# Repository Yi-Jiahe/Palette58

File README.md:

# Palette 58

My first (to-be) split ergonomic keyboard.

4x6 column staggered board with 5 key thumb cluster utilizing low profile switches.

The Palette 58 is meant to be an introductory keyboard, heavily inspired by the Sofle.

It includes a number row and additional outer pinky column to support a wider range of layouts to allow for experimentation.

Compared to the Sofle, it features a more aggressive pinky stagger and no additional flex key.

No LEDs because of the added complexity and cost.

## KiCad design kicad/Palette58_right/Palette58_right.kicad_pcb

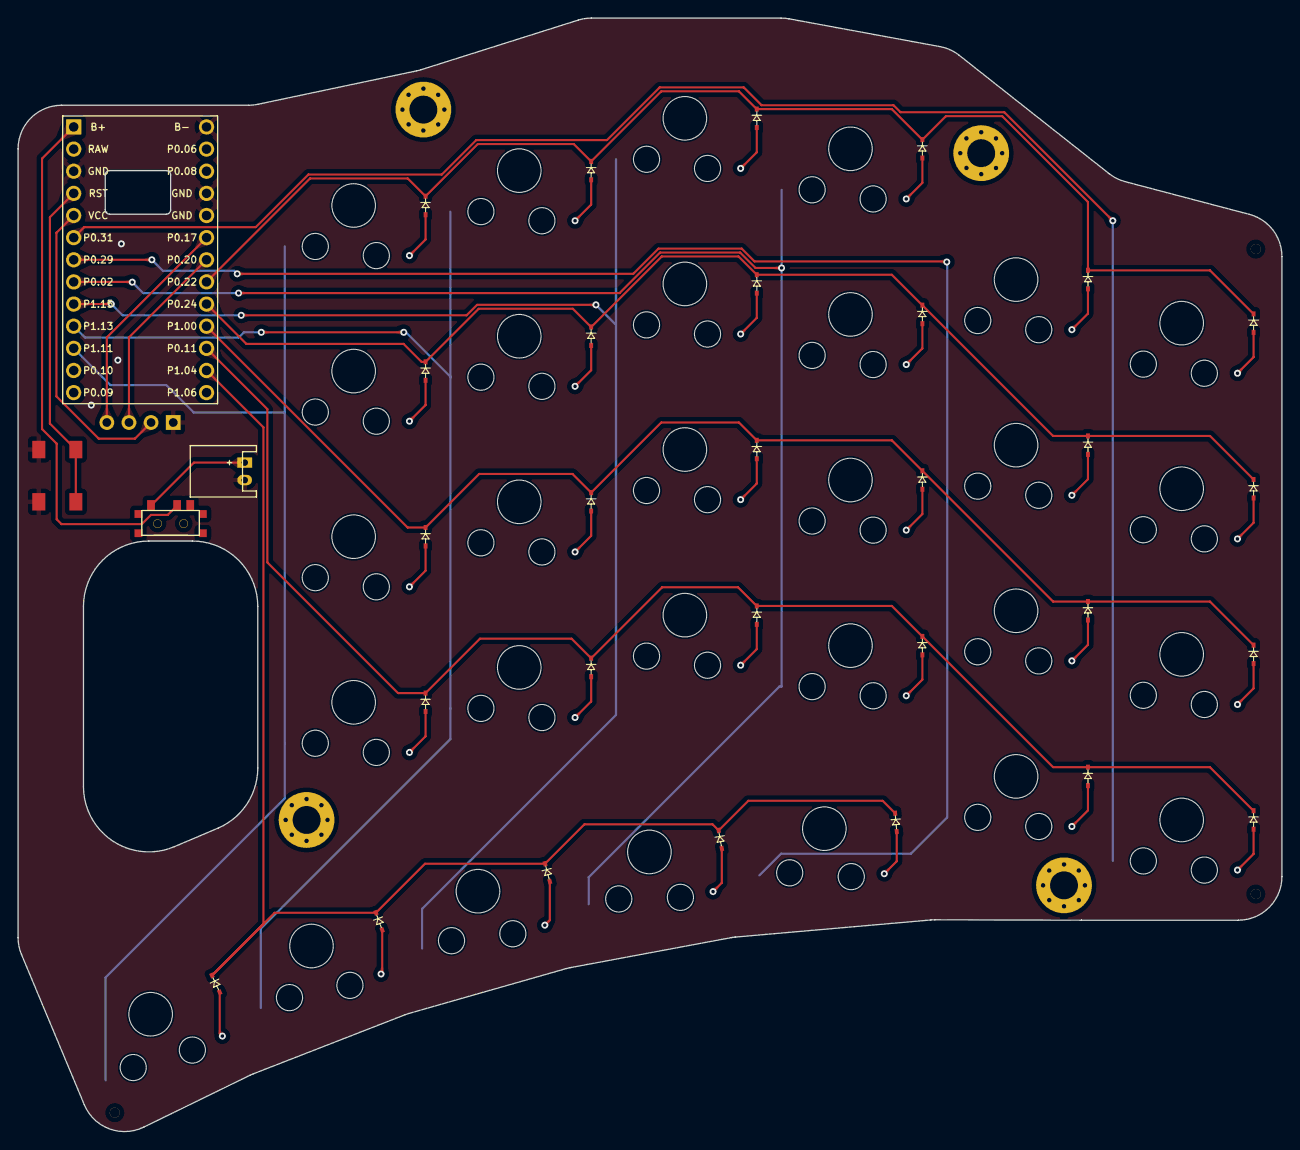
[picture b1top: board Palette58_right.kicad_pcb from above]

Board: 2 copper layers, 145.0 x 127.8 mm, 66 parts (0 on the bottom side), 47 nets.

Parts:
D1, D2, D3, D4, D5, D6, D7, D8, D9, D10, D11, D12, D13, D14, D15, D16, D17, D18, D19, D20, D21, D22, D23, D24, D25, D26, D27, D28, D29: 1N4148; ComboDiode
JST1: JST_PH_S2B-PH-K_02x2.00mm_Angled
MCU1: nice!nanov2
OLED1: OLED; OLED_headers
S1, S2, S3, S4, S5, S6, S7, S8, S9, S10, S11, S12, S13, S14, S15, S16, S17, S18, S19, S20, S21, S22, S23, S24, S25, S26, S27, S28, S29: Gaeteron_low_profile
SW1: MSK12C02-HB; SPDT_C128955
SW2: TS-1187A-B-A-B; PushSwitch
_34, _35, _36: ToolingHole

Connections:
B+: MCU1.1, SW1.2
GND: JST1.2, MCU1.3, MCU1.14, MCU1.17, MCU1.18, OLED1.1, SW2.3, SW2.4
JST+: JST1.1, SW1.1
RST: MCU1.4, SW2.1, SW2.2
SCL: MCU1.20, OLED1.3
SDA: MCU1.19, OLED1.4
VCC: MCU1.5, OLED1.2
col_1: MCU1.6, S1.1, S2.1, S3.1, S4.1
col_2: MCU1.7, S5.1, S6.1, S7.1, S8.1, S25.1
col_3: MCU1.8, S9.1, S10.1, S11.1, S12.1, S26.1
col_4: MCU1.9, S13.1, S14.1, S15.1, S16.1, S27.1
col_5: MCU1.10, S17.1, S18.1, S19.1, S20.1, S28.1
col_6: MCU1.11, S21.1, S22.1, S23.1, S24.1, S29.1
mirror_home_cluster: D28.2, S28.2
mirror_index_bottom: D17.2, S17.2
mirror_index_home: D18.2, S18.2
mirror_index_num: D20.2, S20.2
mirror_index_top: D19.2, S19.2
mirror_inner_bottom: D21.2, S21.2
mirror_inner_cluster: D29.2, S29.2
mirror_inner_home: D22.2, S22.2
mirror_inner_num: D24.2, S24.2
mirror_inner_top: D23.2, S23.2
mirror_middle_bottom: D13.2, S13.2
mirror_middle_home: D14.2, S14.2
mirror_middle_num: D16.2, S16.2
mirror_middle_top: D15.2, S15.2
mirror_outer-2_cluster: D26.2, S26.2
mirror_outer-3_cluster: D25.2, S25.2
mirror_outer_bottom: D1.2, S1.2
mirror_outer_cluster: D27.2, S27.2
mirror_outer_home: D2.2, S2.2
mirror_outer_num: D4.2, S4.2
mirror_outer_top: D3.2, S3.2
mirror_pinky_bottom: D5.2, S5.2
mirror_pinky_home: D6.2, S6.2
mirror_pinky_num: D8.2, S8.2
mirror_pinky_top: D7.2, S7.2
mirror_ring_bottom: D9.2, S9.2
mirror_ring_home: D10.2, S10.2
mirror_ring_num: D12.2, S12.2
mirror_ring_top: D11.2, S11.2
row_1: D4.1, D8.1, D12.1, D16.1, D20.1, D24.1, MCU1.21
row_2: D3.1, D7.1, D11.1, D15.1, D19.1, D23.1, MCU1.22
row_3: D2.1, D6.1, D10.1, D14.1, D18.1, D22.1, MCU1.23
row_4: D1.1, D5.1, D9.1, D13.1, D17.1, D21.1, MCU1.24
row_5: D25.1, D26.1, D27.1, D28.1, D29.1, MCU1.25

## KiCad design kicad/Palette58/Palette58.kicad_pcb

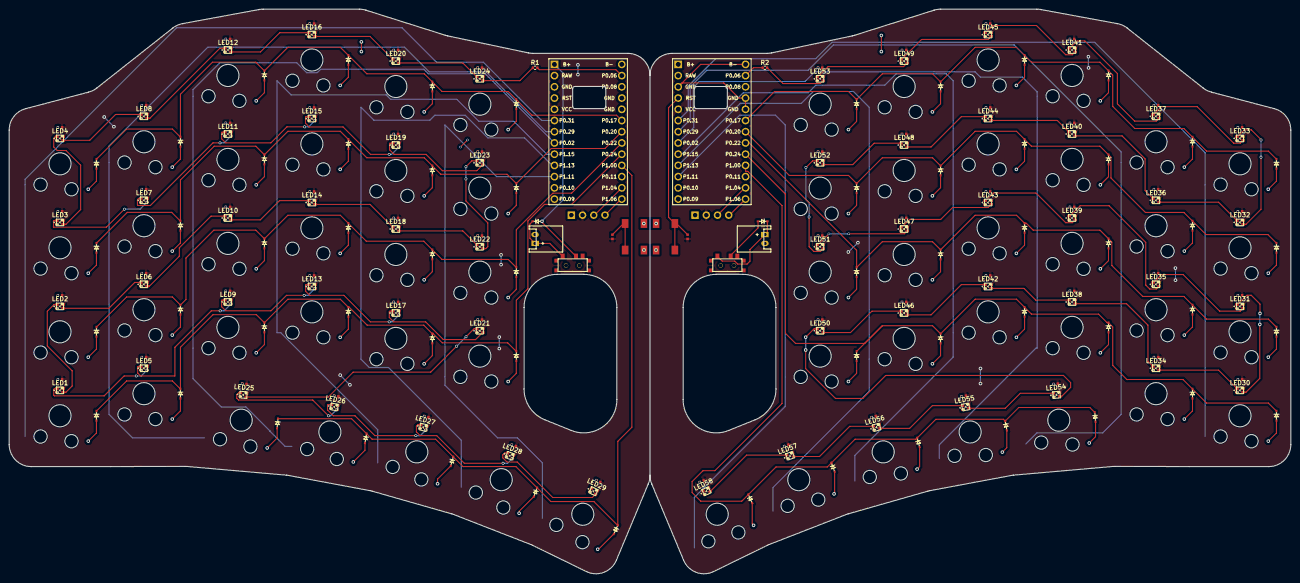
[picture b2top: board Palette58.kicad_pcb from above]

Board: 2 copper layers, 290.0 x 127.8 mm, 248 parts (0 on the bottom side), 140 nets.

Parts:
C1, C2, C3, C4, C5, C6, C7, C8, C9, C10, C11, C12, C13, C14, C15, C16, C17, C18, C19, C20, C21, C22, C23, C24, C25, C26, C27, C28, C29, C30, C31, C32, C33, C34, C35, C36, C37, C38, C39, C40, C41, C42, C43, C44, C45, C46, C47, C48, C49, C50, C51, C52, C53, C54, C55, C56, C57, C58: 100nF; Capacitor
D1, D2, D3, D4, D5, D6, D7, D8, D9, D10, D11, D12, D13, D14, D15, D16, D17, D18, D19, D20, D21, D22, D23, D24, D25, D26, D27, D28, D29, D30, D31, D32, D33, D34, D35, D36, D37, D38, D39, D40, D41, D42, D43, D44, D45, D46, D47, D48, D49, D50, D51, D52, D53, D54, D55, D56, D57, D58: 1N4148; ComboDiode
D59, D60: 1N5819; ComboDiode
JST1, JST2: JST_PH_S2B-PH-K_02x2.00mm_Angled
LED1, LED2, LED3, LED4, LED5, LED6, LED7, LED8, LED9, LED10, LED11, LED12, LED13, LED14, LED15, LED16, LED17, LED18, LED19, LED20, LED21, LED22, LED23, LED24, LED25, LED26, LED27, LED28, LED29, LED30, LED31, LED32, LED33, LED34, LED35, LED36, LED37, LED38, LED39, LED40, LED41, LED42, LED43, LED44, LED45, LED46, LED47, LED48, LED49, LED50, LED51, LED52, LED53, LED54, LED55, LED56, LED57, LED58: XINGLIGHTXL-1615RGBC-WS2812B; XINGLIGHT XL-1615RGBC-WS2812B
MCU1, MCU2: nice!nanov2
OLED1, OLED2: OLED; OLED_headers
R1, R2: 330Ω; R_0402_1005Metric
R3, R4: 10kΩ; Resistor
S1, S2, S3, S4, S5, S6, S7, S8, S9, S10, S11, S12, S13, S14, S15, S16, S17, S18, S19, S20, S21, S22, S23, S24, S25, S26, S27, S28, S29, S30, S31, S32, S33, S34, S35, S36, S37, S38, S39, S40, S41, S42, S43, S44, S45, S46, S47, S48, S49, S50, S51, S52, S53, S54, S55, S56, S57, S58: Gaeteron_low_profile
SW1, SW2: MSK12C02-HB; SPDT_C128955
SW3, SW4: TS-1187A-B-A-B; PushSwitch

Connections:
B+: D59.2, D60.2, MCU1.1, MCU2.1, SW1.2, SW2.2
GND: C1.1, C2.1, C3.1, C4.1, C5.1, C6.1, C7.1, C8.1, C9.1, C10.1, C11.1, C12.1, C13.1, C14.1, C15.1, C16.1, C17.1, C18.1, C19.1, C20.1, C21.1, C22.1, C23.1, C24.1, C25.1, C26.1, C27.1, C28.1, C29.1, C30.1, C31.1, C32.1, C33.1, C34.1, C35.1, C36.1, C37.1, C38.1, C39.1, C40.1, C41.1, C42.1, C43.1, C44.1, C45.1, C46.1, C47.1, C48.1, C49.1, C50.1, C51.1, C52.1, C53.1, C54.1, C55.1, C56.1, C57.1, C58.1, JST1.2, JST2.2, LED1.3 (VSS), LED2.3 (VSS), LED3.3 (VSS), LED4.3 (VSS), LED5.3 (VSS), LED6.3 (VSS), LED7.3 (VSS), LED8.3 (VSS), LED9.3 (VSS), LED10.3 (VSS), LED11.3 (VSS), LED12.3 (VSS), LED13.3 (VSS), LED14.3 (VSS), LED15.3 (VSS), LED16.3 (VSS), LED17.3 (VSS), LED18.3 (VSS), LED19.3 (VSS), LED20.3 (VSS), LED21.3 (VSS), LED22.3 (VSS), LED23.3 (VSS), LED24.3 (VSS), LED25.3 (VSS), LED26.3 (VSS), LED27.3 (VSS), LED28.3 (VSS), LED29.3 (VSS), LED30.3 (VSS), LED31.3 (VSS), LED32.3 (VSS), LED33.3 (VSS), LED34.3 (VSS), LED35.3 (VSS), LED36.3 (VSS), LED37.3 (VSS), LED38.3 (VSS), LED39.3 (VSS), LED40.3 (VSS), LED41.3 (VSS), LED42.3 (VSS), LED43.3 (VSS), LED44.3 (VSS), LED45.3 (VSS), LED46.3 (VSS), LED47.3 (VSS), LED48.3 (VSS), LED49.3 (VSS), LED50.3 (VSS), LED51.3 (VSS), LED52.3 (VSS), LED53.3 (VSS), LED54.3 (VSS), LED55.3 (VSS), LED56.3 (VSS), LED57.3 (VSS), LED58.3 (VSS), MCU1.3, MCU1.14, MCU1.17, MCU1.18, MCU2.3, MCU2.14, MCU2.17, MCU2.18, OLED1.1, OLED2.1, SW3.3, SW3.4, SW4.3, SW4.4
JST+: D59.1, D60.1, JST1.1, JST2.1, SW1.1, SW2.1
unnamed: LED1.4 (DIN), LED2.2 (DOUT)
unnamed: LED1.2 (DOUT), LED5.4 (DIN)
unnamed: LED2.4 (DIN), LED6.2 (DOUT)
unnamed: LED3.4 (DIN), LED4.2 (DOUT)
unnamed: LED3.2 (DOUT), LED7.4 (DIN)
unnamed: LED4.4 (DIN), LED8.2 (DOUT)
unnamed: LED5.2 (DOUT), LED9.4 (DIN)
unnamed: LED10.4 (DIN), LED14.2 (DOUT)
unnamed: LED6.4 (DIN), LED10.2 (DOUT)
unnamed: LED7.2 (DOUT), LED11.4 (DIN)
unnamed: LED11.2 (DOUT), LED15.4 (DIN)
unnamed: LED12.4 (DIN), LED16.2 (DOUT)
unnamed: LED8.4 (DIN), LED12.2 (DOUT)
unnamed: LED9.2 (DOUT), LED13.4 (DIN)
unnamed: LED13.2 (DOUT), LED17.4 (DIN)
unnamed: LED14.4 (DIN), LED18.2 (DOUT)
unnamed: LED15.2 (DOUT), LED19.4 (DIN)
unnamed: LED16.4 (DIN), LED20.2 (DOUT)
unnamed: LED17.2 (DOUT), LED21.4 (DIN)
unnamed: LED18.4 (DIN), LED22.2 (DOUT)
unnamed: LED19.2 (DOUT), LED23.4 (DIN)
unnamed: LED20.4 (DIN), LED24.2 (DOUT)
unnamed: LED21.2 (DOUT), LED25.4 (DIN)
unnamed: LED22.4 (DIN), LED23.2 (DOUT)
unnamed: LED24.4 (DIN), R1.1
unnamed: LED25.2 (DOUT), LED26.4 (DIN)
unnamed: LED26.2 (DOUT), LED27.4 (DIN)
unnamed: LED27.2 (DOUT), LED28.4 (DIN)
unnamed: LED28.2 (DOUT), LED29.4 (DIN)
unnamed: LED30.4 (DIN), LED31.2 (DOUT)
unnamed: LED30.2 (DOUT), LED34.4 (DIN)
unnamed: LED31.4 (DIN), LED35.2 (DOUT)
unnamed: LED32.4 (DIN), LED33.2 (DOUT)
unnamed: LED32.2 (DOUT), LED36.4 (DIN)
unnamed: LED33.4 (DIN), LED37.2 (DOUT)
unnamed: LED34.2 (DOUT), LED38.4 (DIN)
unnamed: LED35.4 (DIN), LED39.2 (DOUT)
unnamed: LED36.2 (DOUT), LED40.4 (DIN)
unnamed: LED37.4 (DIN), LED41.2 (DOUT)
unnamed: LED38.2 (DOUT), LED42.4 (DIN)
unnamed: LED39.4 (DIN), LED43.2 (DOUT)
unnamed: LED40.2 (DOUT), LED44.4 (DIN)
unnamed: LED41.4 (DIN), LED45.2 (DOUT)
unnamed: LED42.2 (DOUT), LED46.4 (DIN)
unnamed: LED43.4 (DIN), LED47.2 (DOUT)
unnamed: LED44.2 (DOUT), LED48.4 (DIN)
unnamed: LED45.4 (DIN), LED49.2 (DOUT)
unnamed: LED46.2 (DOUT), LED50.4 (DIN)
unnamed: LED47.4 (DIN), LED51.2 (DOUT)
unnamed: LED48.2 (DOUT), LED52.4 (DIN)
unnamed: LED49.4 (DIN), LED53.2 (DOUT)
unnamed: LED50.2 (DOUT), LED54.4 (DIN)
unnamed: LED51.4 (DIN), LED52.2 (DOUT)
unnamed: LED53.4 (DIN), R2.2
unnamed: LED54.2 (DOUT), LED55.4 (DIN)
unnamed: LED55.2 (DOUT), LED56.4 (DIN)
unnamed: LED56.2 (DOUT), LED57.4 (DIN)
unnamed: LED57.2 (DOUT), LED58.4 (DIN)
P0.06: MCU1.15, MCU2.15, R1.2, R2.1
P0.08: MCU1.16, MCU2.16
P0.10: MCU1.12, MCU2.12
P0.11: MCU1.24, MCU2.24
P0.90: MCU1.13, MCU2.13
RAW: MCU1.2, MCU2.2
RST: MCU1.4, MCU2.4, R3.2, R4.2, SW3.1, SW3.2, SW4.1, SW4.2
SCL: MCU1.25, MCU2.25, OLED1.3, OLED2.3
SDA: MCU1.26, MCU2.26, OLED1.4, OLED2.4
VCC: C1.2, C2.2, C3.2, C4.2, C5.2, C6.2, C7.2, C8.2, C9.2, C10.2, C11.2, C12.2, C13.2, C14.2, C15.2, C16.2, C17.2, C18.2, C19.2, C20.2, C21.2, C22.2, C23.2, C24.2, C25.2, C26.2, C27.2, C28.2, C29.2, C30.2, C31.2, C32.2, C33.2, C34.2, C35.2, C36.2, C37.2, C38.2, C39.2, C40.2, C41.2, C42.2, C43.2, C44.2, C45.2, C46.2, C47.2, C48.2, C49.2, C50.2, C51.2, C52.2, C53.2, C54.2, C55.2, C56.2, C57.2, C58.2, LED1.1 (VDD), LED2.1 (VDD), LED3.1 (VDD), LED4.1 (VDD), LED5.1 (VDD), LED6.1 (VDD), LED7.1 (VDD), LED8.1 (VDD), LED9.1 (VDD), LED10.1 (VDD), LED11.1 (VDD), LED12.1 (VDD), LED13.1 (VDD), LED14.1 (VDD), LED15.1 (VDD), LED16.1 (VDD), LED17.1 (VDD), LED18.1 (VDD), LED19.1 (VDD), LED20.1 (VDD), LED21.1 (VDD), LED22.1 (VDD), LED23.1 (VDD), LED24.1 (VDD), LED25.1 (VDD), LED26.1 (VDD), LED27.1 (VDD), LED28.1 (VDD), LED29.1 (VDD), LED30.1 (VDD), LED31.1 (VDD), LED32.1 (VDD), LED33.1 (VDD), LED34.1 (VDD), LED35.1 (VDD), LED36.1 (VDD), LED37.1 (VDD), LED38.1 (VDD), LED39.1 (VDD), LED40.1 (VDD), LED41.1 (VDD), LED42.1 (VDD), LED43.1 (VDD), LED44.1 (VDD), LED45.1 (VDD), LED46.1 (VDD), LED47.1 (VDD), LED48.1 (VDD), LED49.1 (VDD), LED50.1 (VDD), LED51.1 (VDD), LED52.1 (VDD), LED53.1 (VDD), LED54.1 (VDD), LED55.1 (VDD), LED56.1 (VDD), LED57.1 (VDD), LED58.1 (VDD), MCU1.5, MCU2.5, OLED1.2, OLED2.2, R3.1, R4.1
col_1: MCU1.6, MCU2.6, S1.1, S2.1, S3.1, S4.1, S30.1, S31.1, S32.1, S33.1
col_2: MCU1.7, MCU2.7, S5.1, S6.1, S7.1, S8.1, S25.1, S34.1, S35.1, S36.1, S37.1, S54.1
col_3: MCU1.8, MCU2.8, S9.1, S10.1, S11.1, S12.1, S26.1, S38.1, S39.1, S40.1, S41.1, S55.1
col_4: MCU1.9, MCU2.9, S13.1, S14.1, S15.1, S16.1, S27.1, S42.1, S43.1, S44.1, S45.1, S56.1
col_5: MCU1.10, MCU2.10, S17.1, S18.1, S19.1, S20.1, S28.1, S46.1, S47.1, S48.1, S49.1, S57.1
col_6: MCU1.11, MCU2.11, S21.1, S22.1, S23.1, S24.1, S29.1, S50.1, S51.1, S52.1, S53.1, S58.1
home_cluster: D28.2, S28.2
index_bottom: D17.2, S17.2
index_home: D18.2, S18.2
index_num: D20.2, S20.2
index_top: D19.2, S19.2
inner_bottom: D21.2, S21.2
inner_cluster: D29.2, S29.2
inner_home: D22.2, S22.2
inner_num: D24.2, S24.2
inner_top: D23.2, S23.2
middle_bottom: D13.2, S13.2
middle_home: D14.2, S14.2
middle_num: D16.2, S16.2
middle_top: D15.2, S15.2
mirror_home_cluster: D57.2, S57.2
mirror_index_bottom: D46.2, S46.2
mirror_index_home: D47.2, S47.2
mirror_index_num: D49.2, S49.2
mirror_index_top: D48.2, S48.2
mirror_inner_bottom: D50.2, S50.2
mirror_inner_cluster: D58.2, S58.2
mirror_inner_home: D51.2, S51.2
mirror_inner_num: D53.2, S53.2
mirror_inner_top: D52.2, S52.2
mirror_middle_bottom: D42.2, S42.2
mirror_middle_home: D43.2, S43.2
mirror_middle_num: D45.2, S45.2
mirror_middle_top: D44.2, S44.2
mirror_outer-2_cluster: D55.2, S55.2
mirror_outer-3_cluster: D54.2, S54.2
mirror_outer_bottom: D30.2, S30.2
mirror_outer_cluster: D56.2, S56.2
mirror_outer_home: D31.2, S31.2
mirror_outer_num: D33.2, S33.2
mirror_outer_top: D32.2, S32.2
mirror_pinky_bottom: D34.2, S34.2
mirror_pinky_home: D35.2, S35.2
mirror_pinky_num: D37.2, S37.2
mirror_pinky_top: D36.2, S36.2
mirror_ring_bottom: D38.2, S38.2
mirror_ring_home: D39.2, S39.2
mirror_ring_num: D41.2, S41.2
mirror_ring_top: D40.2, S40.2
outer-2_cluster: D26.2, S26.2
outer-3_cluster: D25.2, S25.2
outer_bottom: D1.2, S1.2
outer_cluster: D27.2, S27.2
outer_home: D2.2, S2.2
outer_num: D4.2, S4.2
outer_top: D3.2, S3.2
pinky_bottom: D5.2, S5.2
pinky_home: D6.2, S6.2
pinky_num: D8.2, S8.2
pinky_top: D7.2, S7.2
ring_bottom: D9.2, S9.2
ring_home: D10.2, S10.2
ring_num: D12.2, S12.2
ring_top: D11.2, S11.2
row_1: D4.1, D8.1, D12.1, D16.1, D20.1, D24.1, D33.1, D37.1, D41.1, D45.1, D49.1, D53.1, MCU1.19, MCU2.19
row_2: D3.1, D7.1, D11.1, D15.1, D19.1, D23.1, D32.1, D36.1, D40.1, D44.1, D48.1, D52.1, MCU1.20, MCU2.20
row_3: D2.1, D6.1, D10.1, D14.1, D18.1, D22.1, D31.1, D35.1, D39.1, D43.1, D47.1, D51.1, MCU1.21, MCU2.21
row_4: D1.1, D5.1, D9.1, D13.1, D17.1, D21.1, D30.1, D34.1, D38.1, D42.1, D46.1, D50.1, MCU1.22, MCU2.22
row_5: D25.1, D26.1, D27.1, D28.1, D29.1, D54.1, D55.1, D56.1, D57.1, D58.1, MCU1.23, MCU2.23

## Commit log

2024-11-06 Initalize ergogen.yaml
2024-11-06 feature: define gateron low profile footprint
2024-11-06 feature: Add WS2812B-2020
2024-11-06 chore: move diode to right
2024-11-06 feature: Add nice!nano_v2 footprint
2024-11-08 feature: Add nets for cols and rows
2024-11-08 feature: Add nets for SDA and SCL
2024-11-08 feature: add power circuitry
2024-11-08 feature: introduce vias
2024-11-09 chore: Replace WS2812-2020 with easier to place 1615
2024-11-09 chore: adjust power component placements
2024-11-09 feature: add decoupling capacitors
2024-11-09 feature: Add values to diodes
2024-11-09 Add reset button
2024-11-09 Init kicad project
2024-11-10 change smd diode footprint to 323
2024-11-10 add cutouts
2024-11-10 straighten mirrored edge
2024-11-10 Reflect board
2024-11-10 Route simple routes
2024-11-10 Route left half
2024-11-10 Finish Routing
2024-11-12 Split pcb into two projects
2024-11-12 Add mounting holes
2024-11-12 Add tooling holes
2024-11-12 fix: add vias back to left half hotswap pads
2024-11-12 fix: fix capacitor and via placement
2024-11-12 Send left half for production
2024-11-30 fix: Fix via footprint
2024-12-11 Simplify left half
2024-12-11 Update right half
2024-12-12 Send right side for production
